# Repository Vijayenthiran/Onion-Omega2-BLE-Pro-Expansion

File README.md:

## Onion Omega 2 BLE Pro Expansion Board

[Onion Omega 2](https://onion.io/omega2/) is a $5 Linux computer with Wifi support. It is great for developing Internet of Things (IoT) applications. Unfortunately, the board cannot be powered directly as there is no option for USB power. Also, it uses 2 mm pitch headers which makes it impossible to use with a regular breadboard without any converter/expansion board. Even after powering the Omega 2, accessing the terminal should be done through wifi. All these problems make Omega 2 less easy to get started. 

This expansion board addresses the above-mentioned issues with some additional features at a very low cost compared to the expansion boards [available](https://onion.io/product-category/docks/) from Onion Crop directly. 

**Features:**

- Breakout board for Onion Omega 2 (*2.00mm to 2.54mm*).
- Access Onion Omega 2 Terminal without Wifi Connection.
- Adds BLE support to the Omega 2 (*Software support TBD. Contributions welcomed*).
- Standalone BLE device HM-11 (*Throught Serial AT Commands*). 
- Standalone USB to Serial programmer/debugger. 
- Program any Arduino or ESP8266.
- 5V to 3.3V converter (*Up to 700mA*).
- Onboard RGB LED.
- Contains both USB A Male and Micro USB female (*Selectable via jumpers*).

**Getting Started:**
- Install [CH340G driver](https://sparks.gogo.co.nz/ch340.html) *before* plugging into your computer. Restart the computer if required.
- Plug your Onion Omega 2 into the 2.00mm header. Make sure you plug in the correct orientation (Onion Logo should face the USB port).
- Get to know how to access USB Serial devices. Here are some recommended articles: [Windows](https://software.intel.com/en-us/setting-up-serial-terminal-on-system-with-windows) | [Linux](https://stackoverflow.com/a/6719367) | [Mac](https://software.intel.com/en-us/setting-up-serial-terminal-on-system-with-mac-os-x)
- Open the Serial Console and wait for some time (usually 2 to 3 mins) for the Omega 2 to boot up. You will see a lot of messages like this:
  
- Press Enter key twice. You are good to go. Head over to [Onion Omega 2 Documentation page](https://docs.onion.io/omega2-docs/connecting-to-the-omega-terminal.html#connecting-to-the-omega-terminal-serial) for more information. 

**RGB LED demo**:
- Install [python](https://wiki.onion.io/Tutorials/Installing-Python).
- Enter the command `cd root` and press enter.
- Type `vi RGBDemo.py` and press `i` key.
- Copy paste this code:
```
    import onionGpio
    # for delay
    import time

    # Create GPIO object
    gpioObject17 = onionGpio.OnionGpio(17)
    gpioObject16 = onionGpio.OnionGpio(16)
    gpioObject15 = onionGpio.OnionGpio(15)

    time.sleep(0.01)

    status = gpioObject17.setOutputDirection(1)
    status = gpioObject16.setOutputDirection(1)
    status = gpioObject15.setOutputDirection(1)

    while True:
        for r in range(0,2):
            for g in range(0,2):
                for b in range(0,2):
                    status = gpioObject17.setOutputDirection(r)
                    status = gpioObject16.setOutputDirection(g)
                    status = gpioObject15.setOutputDirection(b)
                    time.sleep(0.01)
```
- Press `ESC` key and press `:wq` and press enter. Now your file will be saved.
- Enter the command `python RGBDemo.py` and press enter. You should see your RGB enter changing its color.
- To terminate the demo press `CTRL + C`.

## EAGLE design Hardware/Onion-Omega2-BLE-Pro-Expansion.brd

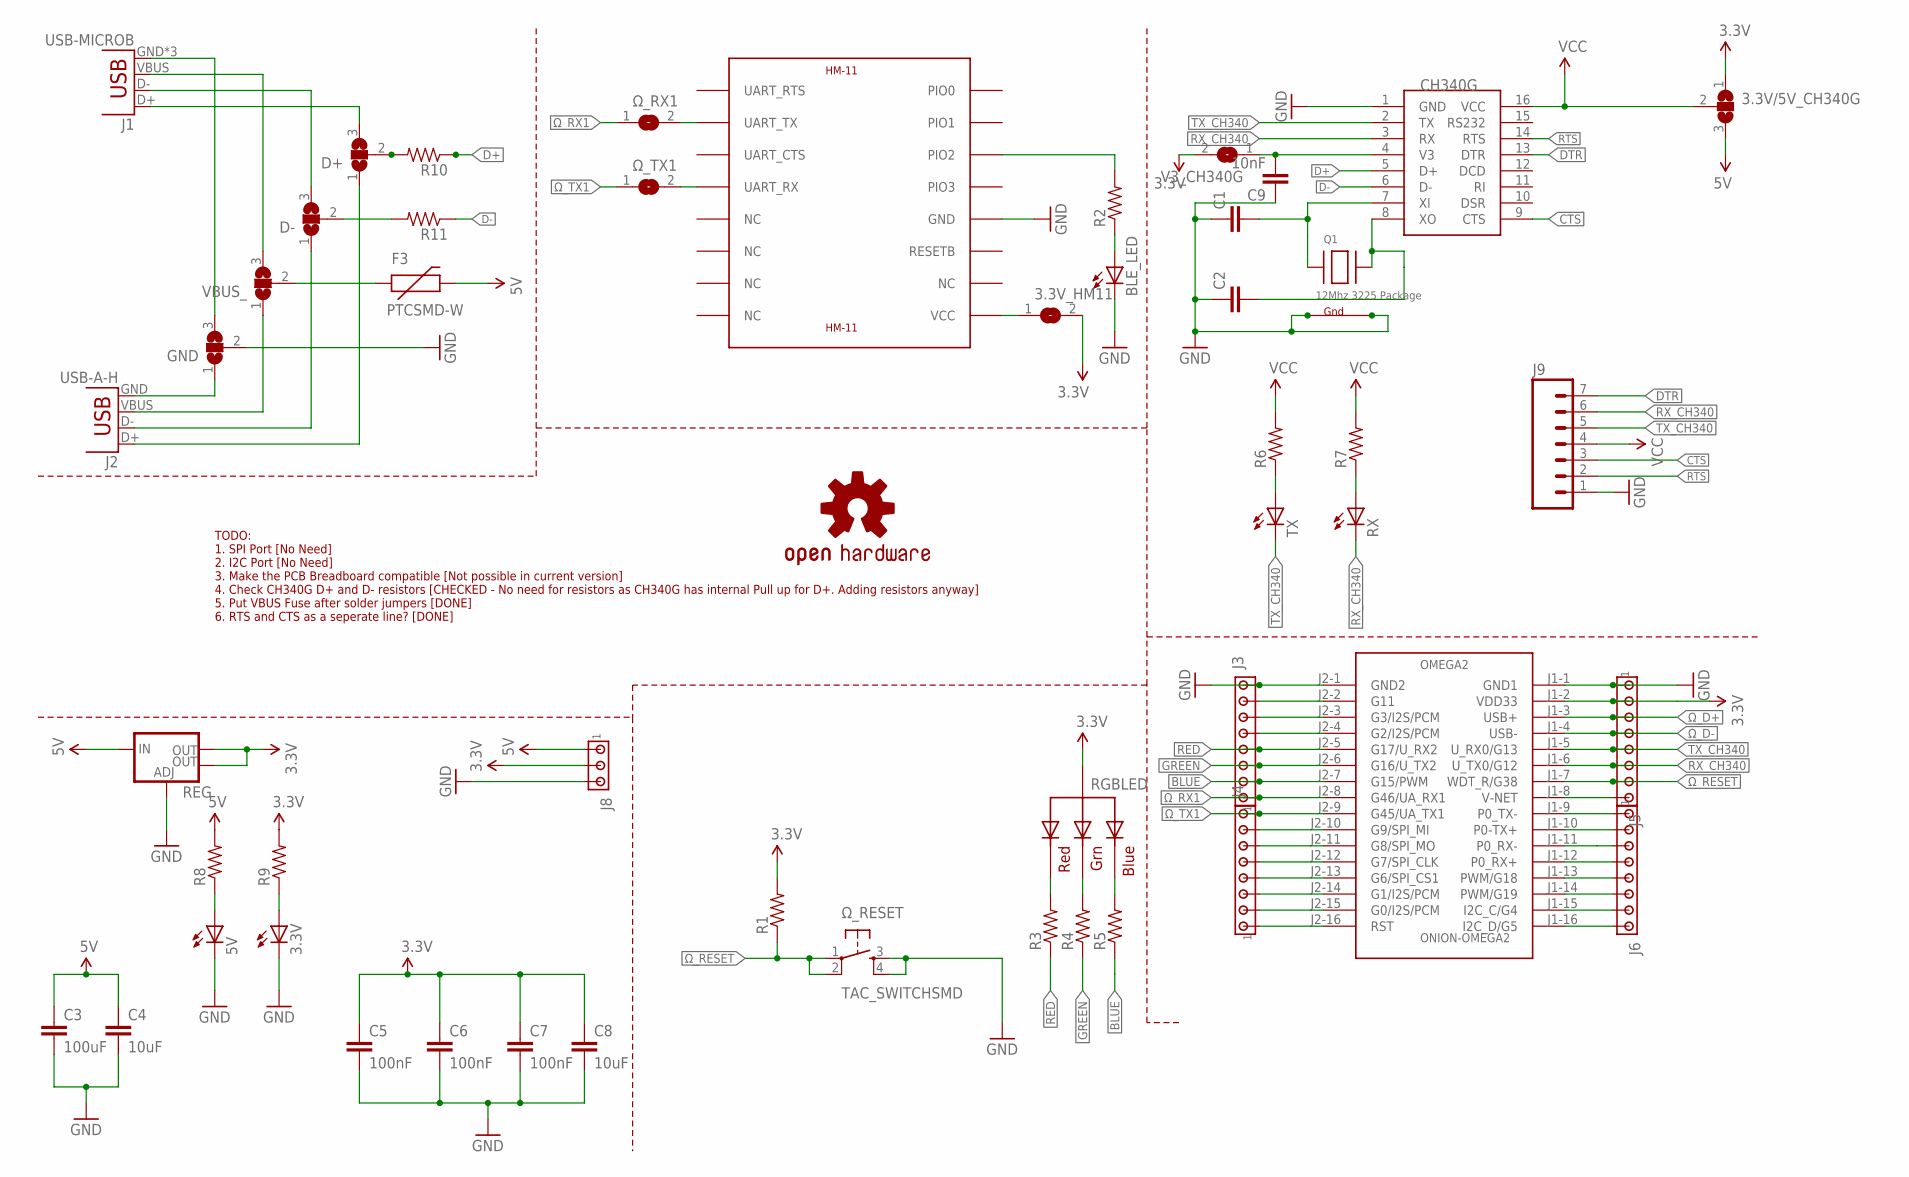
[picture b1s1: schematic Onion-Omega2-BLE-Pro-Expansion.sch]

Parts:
3.3V, 5V: LEDCHIPLED_1206; CHIPLED_1206
3.3V/5V_CH340G: SJ2W; SJ_2
3.3V_HM11: SJ
BLE_LED: LEDCHIPLED_1206; CHIPLED_1206
C1, C2: CAP1206; 1206
C3: 100uF; 1206
C4, C8: 10uF; 1206
C5, C6, C7: 100nF; 1206
C9: 10nF; 1206
D+: SJ2W; SJ_2
D-: SJ2W; SJ_2
F3: PTCSMD-W; PTC-1206-WIDE
GND: SJ2W; SJ_2
J1: USB-MICROB
J2: USB-A-H
J3, J4, J5, J6: MTA08-100; 10X08MTA
J8: MTA03-100; 10X03MTA
J9: M07SMD; 1X07-SMD-FEMALE-V2
LOGO1: OSHW-LOGOMINI; OSHW-LOGO-MINI
OMEGA2: ONION-OMEGA2; ONION-2MM-2X16
Q1: 12Mhz 3225 Package; NX3225
R1, R2, R3, R4, R5, R6, R7, R8, R9: RESISTOR1206; 1206
R10, R11: RESISTOR0805-RES; 0805
REG: V_REG_LM1117SOT223; SOT223
RGBLED: RGBLED_CA-PIRANHA; PIRANHA5MM
RX: LEDCHIPLED_1206; CHIPLED_1206
TX: LEDCHIPLED_1206; CHIPLED_1206
U$1: CH340G; SOIC16
U$2: HM-11
V3_CH340G: SJ
VBUS_: SJ2W; SJ_2
Ω_RESET: TAC_SWITCHSMD; TACTILE-SWITCH-SMD
Ω_RX1: SJ
Ω_TX1: SJ

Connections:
3.3V: 3.3V/5V_CH340G.1, 3.3V_HM11.2, C5.1, C6.1, C7.1, C8.1, J5.2, J8.2, OMEGA2.J1-2 (VDD33), R1.2, R9.2, REG.2 (OUT), REG.4 (OUT), RGBLED.4 (VCC), V3_CH340G.2
5V: 3.3V/5V_CH340G.3, C3.1, C4.1, F3.2, J8.1, R8.2, REG.3 (IN)
BLUE: J3.2, OMEGA2.J2-7 (G15/PWM), R5.1
CTS: J9.3, U$1.9 (CTS)
D+: R10.1, U$1.5 (D+)
D-: R11.1, U$1.6 (D-)
DTR: J9.7, U$1.13 (DTR)
GND: 3.3V.C, 5V.C, BLE_LED.C, C1.1, C2.1, C3.2, C4.2, C5.2, C6.2, C7.2, C8.2, C9.1, GND.2, J3.8, J5.1, J8.3, J9.1, OMEGA2.J1-1 (GND1), OMEGA2.J2-1 (GND2), Q1.2 (G2), Q1.4 (G1), REG.1 (ADJ), U$1.1 (GND), U$2.GND, Ω_RESET.3, Ω_RESET.4
GREEN: J3.3, OMEGA2.J2-6 (G16/U_TX2), R4.1
unnamed: C1.2, Q1.1 (X1), U$1.7 (XI)
unnamed: C2.2, Q1.3 (X2), U$1.8 (XO)
unnamed: R2.2, U$2.PIO2
unnamed: BLE_LED.A, R2.1
unnamed: U$2.UART_TX, Ω_RX1.2
unnamed: J3.7, OMEGA2.J2-2 (G11)
unnamed: J3.6, OMEGA2.J2-3 (G3/I2S/PCM)
unnamed: J3.5, OMEGA2.J2-4 (G2/I2S/PCM)
unnamed: C9.2, U$1.4 (V3), V3_CH340G.1
unnamed: R6.1, TX.A
unnamed: U$2.UART_RX, Ω_TX1.2
unnamed: 3.3V_HM11.1, U$2.VCC
unnamed: J4.7, OMEGA2.J2-10 (G9/SPI_MI)
unnamed: J4.6, OMEGA2.J2-11 (G8/SPI_MO)
unnamed: J4.5, OMEGA2.J2-12 (G7/SPI_CLK)
unnamed: J4.4, OMEGA2.J2-13 (G6/SPI_CS1)
unnamed: J4.3, OMEGA2.J2-14 (G1/I2S/PCM)
unnamed: J4.2, OMEGA2.J2-15 (G0/I2S/PCM)
unnamed: J4.1, OMEGA2.J2-16 (RST)
unnamed: R3.2, RGBLED.2 (RED)
unnamed: R4.2, RGBLED.3 (GREEN)
unnamed: R5.2, RGBLED.1 (BLUE)
unnamed: R7.1, RX.A
unnamed: 5V.A, R8.1
unnamed: 3.3V.A, R9.1
unnamed: F3.1, VBUS_.2
unnamed: J5.8, OMEGA2.J1-8 (V-NET)
unnamed: J6.1, OMEGA2.J1-9 (P0_TX-)
unnamed: J6.2, OMEGA2.J1-10 (P0-TX+)
unnamed: J6.3, OMEGA2.J1-11 (P0_RX-)
unnamed: J6.4, OMEGA2.J1-12 (P0_RX+)
unnamed: J6.5, OMEGA2.J1-13 (PWM/G18)
unnamed: J6.6, OMEGA2.J1-14 (PWM/G19)
unnamed: J6.7, OMEGA2.J1-15 (I2C_C/G4)
unnamed: J6.8, OMEGA2.J1-16 (I2C_D/G5)
unnamed: J2.VBUS, VBUS_.1
unnamed: D+.2, R10.2
unnamed: GND.1, J2.GND
unnamed: GND.3, J1.GND, J1.MT1 (GND), J1.MT2 (GND)
unnamed: J1.VBUS, VBUS_.3
unnamed: D-.3, J1.D-
unnamed: D+.3, J1.D+
unnamed: D-.2, R11.2
unnamed: D-.1, J2.D-
unnamed: D+.1, J2.D+
RED: J3.4, OMEGA2.J2-5 (G17/U_RX2), R3.1
RTS: J9.2, U$1.14 (RTS)
RX_CH340: J5.6, J9.6, OMEGA2.J1-6 (U_TX0/G12), RX.C, U$1.3 (RX)
TX_CH340: J5.5, J9.5, OMEGA2.J1-5 (U_RX0/G13), TX.C, U$1.2 (TX)
VCC: 3.3V/5V_CH340G.2, J9.4, R6.2, R7.2, U$1.16 (VCC)
Ω_D+: J5.3, OMEGA2.J1-3 (USB+)
Ω_D-: J5.4, OMEGA2.J1-4 (USB-)
Ω_RESET: J5.7, OMEGA2.J1-7 (WDT_R/G38), R1.1, Ω_RESET.1, Ω_RESET.2
Ω_RX1: J3.1, OMEGA2.J2-8 (G46/UA_RX1), Ω_RX1.1
Ω_TX1: J4.8, OMEGA2.J2-9 (G45/UA_TX1), Ω_TX1.1

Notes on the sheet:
TODO: 1. SPI Port [No Need] 2. I2C Port [No Need] 3. Make the PCB Breadboard compatible [Not possible in current version] 4. Check CH340G D+ and D- resistors [CHECKED - No need for resistors as CH340G has internal Pull up for D+. Adding resistors anyway] 5. Put VBUS Fuse after solder jumpers [DONE]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

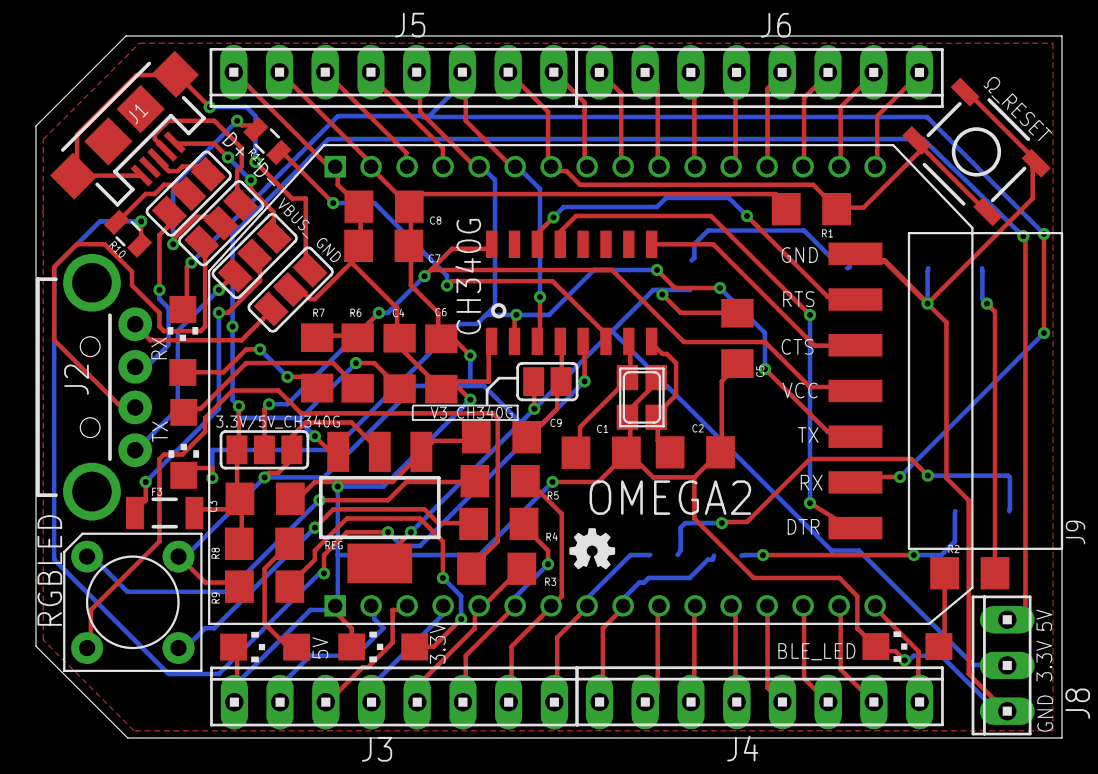
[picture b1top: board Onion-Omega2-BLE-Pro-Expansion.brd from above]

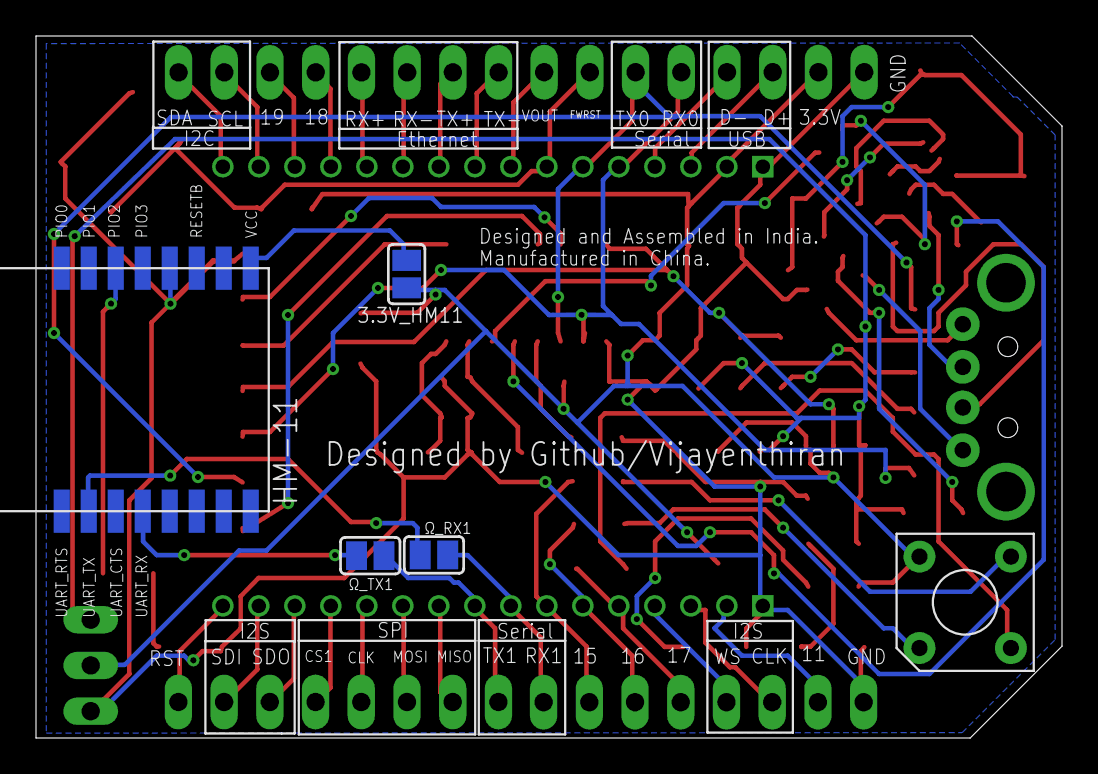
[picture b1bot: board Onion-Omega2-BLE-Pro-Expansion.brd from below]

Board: 2 copper layers, 57.0 x 39.0 mm, 51 parts (4 on the bottom side), 64 nets.

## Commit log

2017-05-01 Fixed symlink
2017-05-01 Board Size reduced. Replaced almost all PTH with SMD. CH340G breakout. Minor improvements. Halfway manual routing. Lots of DRC errors
2017-05-02 Routing done with the help of autorouter. Not satisfied with few components placements
2017-05-02 v0.1 freeze. Placements looks good.
2017-05-24 Silk Screen Fix
2017-05-24 Added CTS/RTS selectino jumper for CH340G breakout
2017-05-26 VBUS fused moved after jumper. Resistors for D+ and D- Lines. TODO: Reduce D+ line length
2017-06-06 CTS and RTS lines seperated. Sent for production
2017-09-16 Adds README and Images
2017-09-16 Updates README
2017-09-16 Image Orientation Fix

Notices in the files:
parts and their libraries:
SparkFun-Connectors: Licensing: Creative Commons ShareAlike 4.0 International - https://creativecommons.org/licenses/by-sa/4.0
